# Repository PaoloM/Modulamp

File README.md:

# Modulamp
A modular concept for a streaming + amplifier box.

## BOM

* Chassis (including transparent window)
* 2x Knobs for volume and mode
* 4x Speaker posts
* 4x RCA inputs
* Raspberry Pi (3B+ or better)
* HifiBerry DAC+ DSP
* Wemos D1 mini
* 5" DSI display
* 0.98" OLED display
* 2x LM3914 bar graph drivers
* 2x 10 segments LED bar graph displays
* 3x 5v relays

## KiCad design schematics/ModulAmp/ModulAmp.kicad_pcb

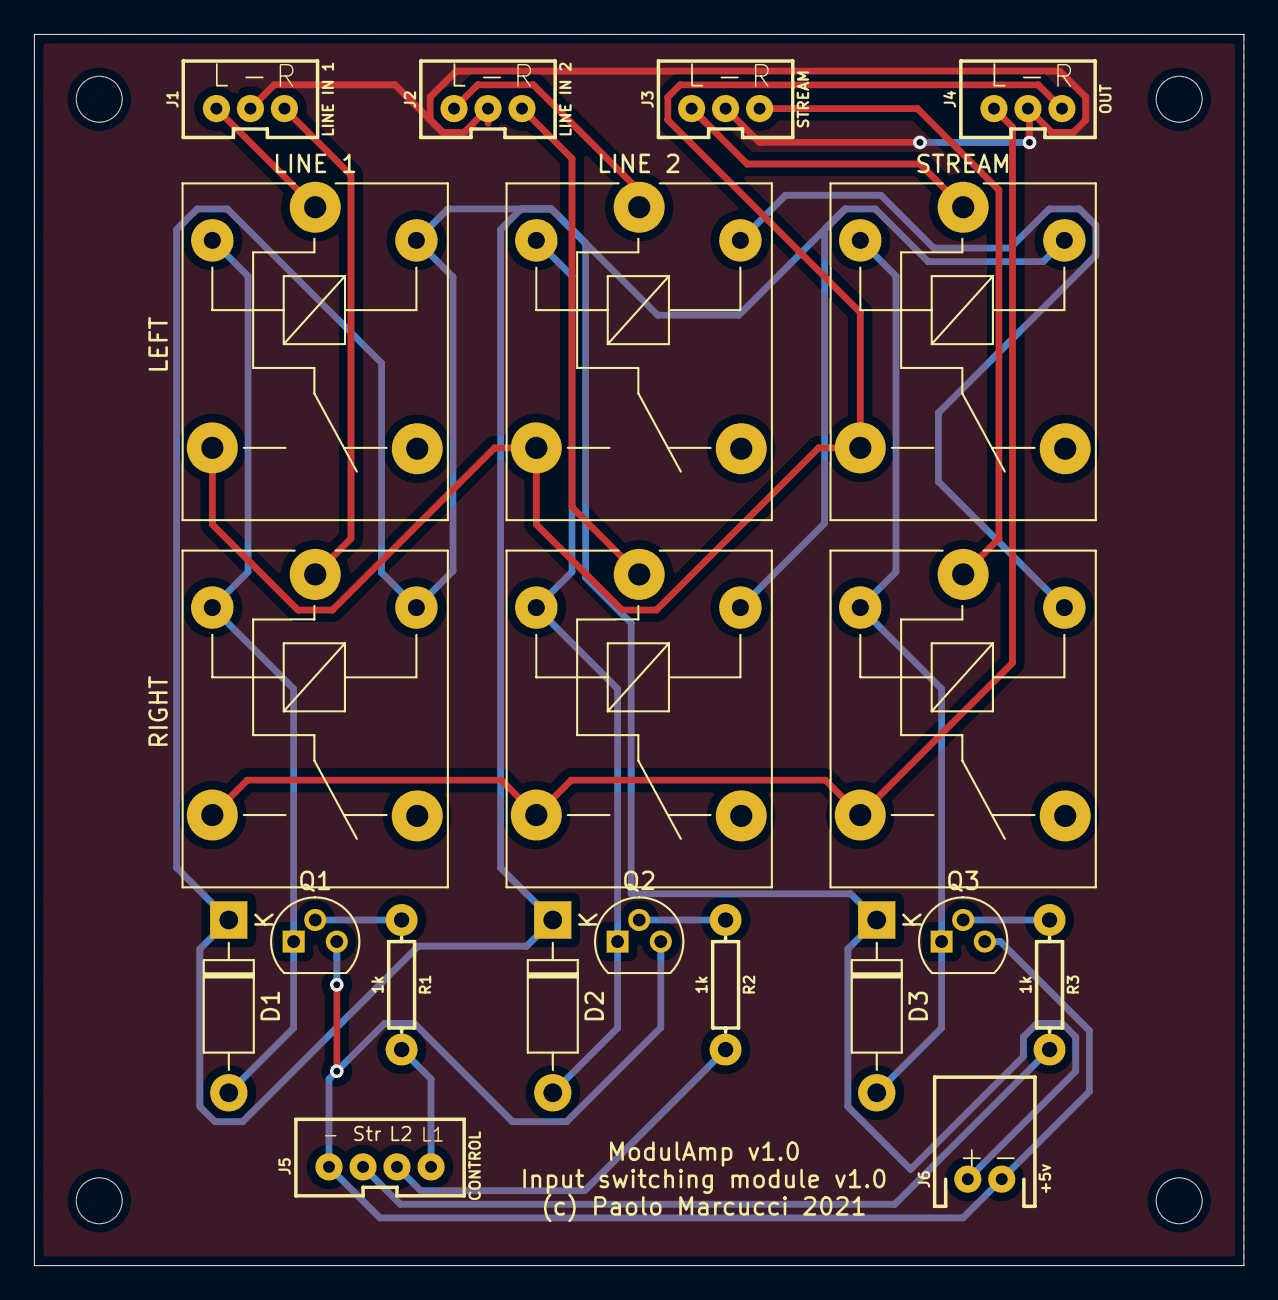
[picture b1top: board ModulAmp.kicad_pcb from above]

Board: 2 copper layers, 71.1 x 72.4 mm, 21 parts (0 on the bottom side), 21 nets.

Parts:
D1, D2, D3: 1N4007; D_DO-41_SOD81_P10.16mm_Horizontal
J1: LINE IN 1; JST-3-PTH-VERT
J2: LINE IN 2; JST-3-PTH-VERT
J3: STREAM; JST-3-PTH-VERT
J4: OUT; JST-3-PTH-VERT
J5: CONTROL; JST-4-PTH-VERT
J6: +5v; JST-2-PTH
K3: LINE 2 RIGHT; Relay_SPDT_SANYOU_SRD_Series_Form_C
K4: LINE 2; Relay_SPDT_SANYOU_SRD_Series_Form_C
K5: STREAM RIGHT; Relay_SPDT_SANYOU_SRD_Series_Form_C
K6: STREAM; Relay_SPDT_SANYOU_SRD_Series_Form_C
LEFT: LINE 1; Relay_SPDT_SANYOU_SRD_Series_Form_C
Q1, Q2, Q3: 2N2222A; TO-92
R1, R2, R3: 1k; AXIAL-0.3
RIGHT: LINE 1 RIGHT; Relay_SPDT_SANYOU_SRD_Series_Form_C

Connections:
GNDA: J1.2, J2.2, J3.2, J4.2
GNDD: J5.1, J6.2, Q1.3, Q2.3, Q3.3
unnamed: D1.1, D2.1, D3.1, J6.1, K3.5, K6.5, LEFT.5, RIGHT.5
unnamed: D1.2, LEFT.2, Q1.1, RIGHT.2
unnamed: D2.2, K3.2, K4.2, Q2.1
unnamed: D3.2, K5.2, K6.2, Q3.1
unnamed: J1.1, LEFT.1
unnamed: J1.3, RIGHT.1
unnamed: J2.1, K4.1
unnamed: J2.3, K3.1
unnamed: J3.1, K6.1
unnamed: J3.3, K5.1
unnamed: J4.1, K3.3, K5.3, RIGHT.3
unnamed: J4.3, K4.3, K6.3, LEFT.3
unnamed: J5.2, R3.P$2
unnamed: J5.3, R2.P$2
unnamed: J5.4, R1.P$2
unnamed: K4.5, K5.5
unnamed: Q1.2, R1.P$1
unnamed: Q2.2, R2.P$1
unnamed: Q3.2, R3.P$1

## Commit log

2021-12-22 First working system, new kicad assets
2021-12-23 Polished interactions, added cmd handling
2022-01-03 Added kicad files
2022-01-03 Added initial schematics
2022-01-04 Fixed input mqtt setting
2022-01-08 Refactored strings and added DHTxx full support
2022-01-14 Removed DHT config and added current input display
2022-01-27 Extra backup
2022-01-28 Added config for EEPROM, new kicad backups
2022-01-28 Added a few references, updated libraries
2022-01-31 Updated SSD1306 I2C to use HW
2022-02-22 Added some debug statements
2022-03-09 Working prototype for KY040, SSD1306 and input sel
2022-03-09 Updated merge conflict
2022-03-11 Added temp support
2022-03-14 Added cpp extension pack
2022-04-28 Added ntp support and LastTime topic format update
2022-11-22 Removed DHT sensor
